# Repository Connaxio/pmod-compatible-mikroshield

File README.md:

# Pmod<sup>TM</sup> Compatible mikroShield
The Pmod<sup>TM</sup> Compatible mikroShield is a mikroBUS<sup>TM</sup> to Digilent Pmod<sup>TM</sup> Compatible add-on board. It further increases the compatibility of mikroBUS<sup>TM</sup> mainboards by adding compatibility with any board that complies with the Digilent Pmod<sup>TM</sup> Interface Specification.

The Digilent Pmod<sup>TM</sup> Compatible connector provides 8 signal pins and 4 power pins that can also be used with breadboard jumper cables to connect many breakout boards, such as the ones distributed by Adafruit and SparkFun.

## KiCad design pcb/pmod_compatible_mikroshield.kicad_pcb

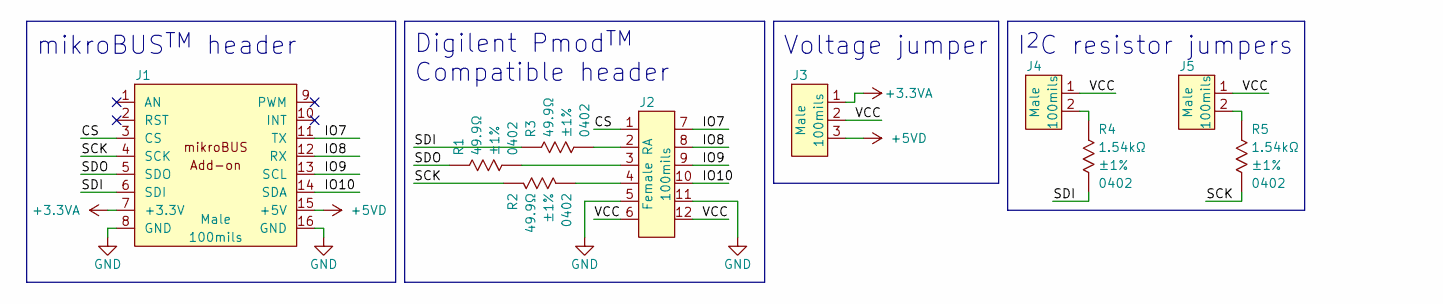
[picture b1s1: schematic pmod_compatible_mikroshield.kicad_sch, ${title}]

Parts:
J1: CON_HDR_MIKROBUS_ADDON_TH; Voltage 350V
J2: CON_HDR_100MILS_F_TH_RA_2X6; Voltage 350V
J3: CON_HDR_100MILS_M_TH_1X3; Voltage 350V
J4, J5: CON_HDR_100MILS_M_TH_1X2; Voltage 350V
R1, R2, R3: RES_49.9Ω_1%_0402; RES_0402_1005M; Tolerance ±1%; Voltage 50V; Manufacturer Part Number RMCF0402FT49R9
R4, R5: RES_1.54KΩ_1%_0402; RES_0402_1005M; Tolerance ±1%; Voltage 50V; Manufacturer Part Number RMCF0402FT1K54

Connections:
+3.3VA: J1.7 (+3.3V), J3.1
+5VD: J1.15 (+5V), J3.3
/CS: J1.3 (CS), J2.1
/IO7: J1.11 (TX), J2.7
/IO8: J1.12 (RX), J2.8
/IO9: J1.13 (SCL), J2.9
/IO10: J1.14 (SDA), J2.10
/SCK: J1.4 (SCK), R2.1, R5.2
/SDI: J1.6 (SDI), R3.1, R4.2
/SDO: J1.5 (SDO), R1.1
/VCC: J2.6, J2.12, J3.2, J4.1, J5.1
GND: J1.8 (GND), J1.16 (GND), J2.5, J2.11
unnamed: J2.2, R3.2
unnamed: J2.3, R1.2
unnamed: J2.4, R2.2
unnamed: J4.2, R4.1
unnamed: J5.2, R5.1

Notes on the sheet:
Voltage jumper
Digilent Pmod^{TM} Compatible header
mikroBUS^{TM} header
I^{2}C resistor jumpers

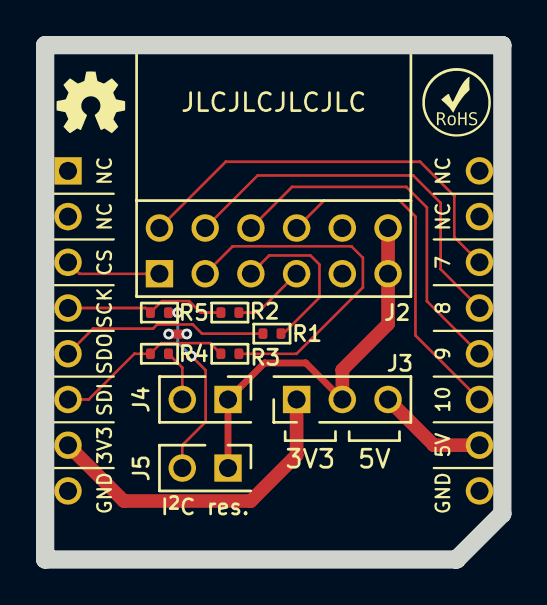
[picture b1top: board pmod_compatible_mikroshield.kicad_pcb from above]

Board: 2 copper layers, 25.4 x 28.6 mm, 10 parts (0 on the bottom side), 17 nets.

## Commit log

2022-05-09 Add oshw logo.
2022-05-12 Silkscreen fixes
2022-05-29 Fix name compliance with Pmod license Add RoHS logo Fix pin names
2022-05-30 Fix inverted SDO/SDI Add source resistors to signal lines
2022-05-30 Add Digilent SF3 SPI flash working example
2022-06-01 Add Pmod license Update README.md
2022-10-13 Fix paste mask and license

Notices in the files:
pcb/pmod_compatible_mikroshield.kicad_pcb:
Licensed under
CERN-OHL-W v2
